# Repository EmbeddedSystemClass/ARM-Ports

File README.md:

Ports of some Communications Libraries to libopencm3
----------------------------------------------------

This project describes ports of CANfestival, FreeRTOS and freeMODBUS libraries
to work with libopencm3. ChaN's FAT filesystem has also been adapted to
libopencm3 but this is not maintained here. Refer to the [Battery Management
System repository](https://github.com/ksarkies/Battery-Management-System/tree/master/chan-fat-stm32-loc3).

In addition there are a number of sample programs designed to run with the
ET-STM32-STAMP and ET-STM32F103 development boards, and the STM32F4-Discovery
board.

* CanFestival-test
* FreeRTOS-usart-libopencm3
* test-can-ETSTM32STAMP
* test-cli
* test-libopencm3-stm32f1
* test-libopencm3-stm32f4
* test-sd-card-spi

More information is provided at:

(http://www.jiggerjuice.info/electronics/projects/arm/canfestival-stm32f103-port.html)

(http://www.jiggerjuice.info/electronics/projects/arm/freertos-stm32f103-port.html)

(http://www.jiggerjuice.info/electronics/projects/arm/modbus-stm32f103-port.html)

(http://www.jiggerjuice.info/electronics/projects/arm/chanfat-stm32f103-port.html)

(c) K. Sarkies 29/06/2015

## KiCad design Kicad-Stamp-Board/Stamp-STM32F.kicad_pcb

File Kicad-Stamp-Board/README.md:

STAMP Board for STM32F
----------------------

This project provides a STAMP board that is pin compatible with the ETT
ET-ARM-STAMP-STM32F103. This has advantages that it can be built into a
prototype system to provide the basic processor functions without having to
commit to any particular processor nor produce PCBs until the system under
development has been proven. The board improves on the ETT board by allowing
a range of processor families.

The board takes certain STM32F processors that use the LQFP64 footprint, as
these are largely pin compatible amongst a number of different families within
the STM32 range. Examples are:

STM32F10x. J5, J6, C15, C16 must all be shorted.
STM32L15x. J5, J6, C15, C16 must all be shorted.
STM32F2xx. J5, J6 must be shorted. C15 and C16 are 2.2uF capacitors.
STM32F4xx. J5, J6 must be shorted. C15 and C16 are 2.2uF capacitors.
STM32F72x. J5, J6, C15, C16 must all be shorted.
STM32F05x. Only C16 must be shorted, C15 and J5, J6, J14 left open.
STM32F30x. J5, C15, C16 must all be shorted, J6 left open.

STM32F37x and STM32F73x are not compatible as pin order is different.

In the second revision of the board, J5 on pin 48 and J6 on pin 18 are provided
so that STM32F05x and STM32F30x can be accommodated.

For any particular processor family, care must be taken to ensure full
compatibility with the board.

The Intersil ICL3221 was selected for RS232 driver as it is has low power
consumption and automatically powers down when no RS232 signals are detected.
It provides a single Rx/Tx pair. It also has the option to allow an external
signal to force power down but this is not used here. This single RS232
interface is provided mainly for programming.

For testing, when the PC serial cable is inserted, the Tx input from that sits
at about -6V. This triggers the device charge pumps to work. The voltages
expected are:

Pin 1 Enable Inv            Gnd
Pin 2 C1+ (C10)            5.96V
Pin 3 V+  (C12)            6.12V
Pin 4 C1- (C10)            3.1V
Pin 5 C2- (C14)            5.78V
Pin 6 C2+ (C14)            -0.3V
Pin 7 V-  (C13)            -5.6V
Pin 8 Tx in                -6V

(c) K. Sarkies 15/02/2018

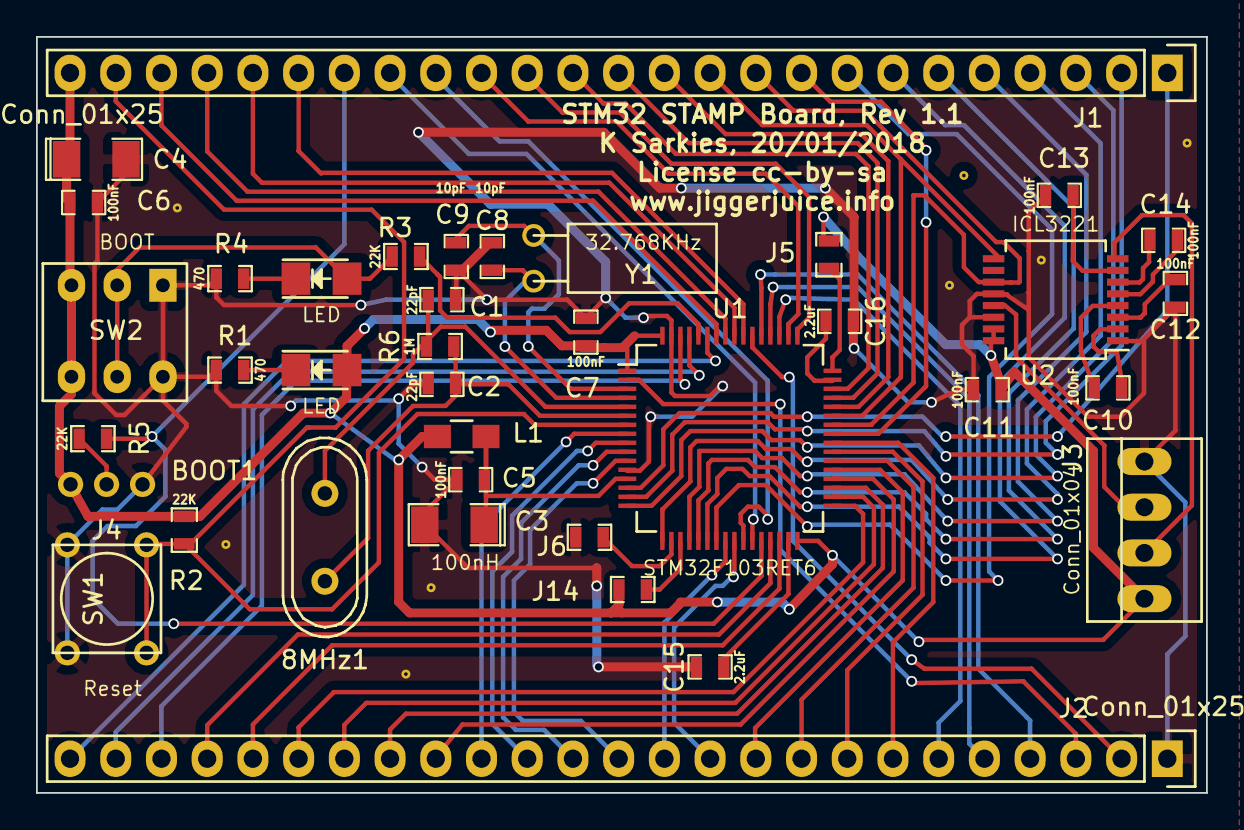
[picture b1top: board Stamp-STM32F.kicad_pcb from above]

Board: 2 copper layers, 65.0 x 42.0 mm, 46 parts (0 on the bottom side), 73 nets.

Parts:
8MHz1: 8MHz; Crystal_HC49-U_Vertical
C1, C2: 22pF; SM0603_Capa
C3, C4: 10uF; SM1206POL
C5, C6, C7, C10, C11, C12, C13, C14: 100nF; SM0603_Capa
C8, C9: 10pF; SM0603_Capa
C15, C16: 2.2uF; SM0603_Capa
D1, D2: LED; LED_1206
J1, J2: Conn_01x25; Pin_Header_Straight_1x25
J3: Conn_01x04; PINHEAD1-4
J4: BOOT1; pin_header_2mm_1x3
J5, J6, J14: Jumper; SM0603_Resistor
J7, J8, J9, J10, J11, J12, J13: Conn_01x01; THROUGHVIA
L1: 100nH; R_0805
R1, R4: 470; SM0603_Resistor
R2, R3, R5: 22K; SM0603_Resistor
R6: 1M; SM0603_Resistor
Ref**: Val**; THROUGHVIA
SW1: Reset; SW_PUSH_TINY
SW2: BOOT; SW_PB_DPDT
U1: STM32F103RET6; LQFP-64_10x10mm_Pitch0.5mm
U2: ICL3221; SSOP-16
Y1: 32.768KHz; Crystal_Watch

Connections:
3.3V: C4.1, C6.2, C7.1, C11.2, D1.2, J1.25, J3.1, J4.1, J5.2, J14.2, L1.1, R2.1, SW2.3, SW2.6, U1.1, U1.32, U1.64, U2.15, U2.16
Boot0: R3.2, U1.60
Earth: C1.2, C2.2, C3.2, C4.2, C5.1, C6.1, C7.2, C8.2, C9.2, C11.1, C12.2, C13.1, C15.2, C16.2, J2.1, J3.4, J4.3, J6.2, J7.1, J8.1, J9.1, J10.1, J11.1, J12.1, J13.1, R1.2, R4.1, SW1.1, SW2.1, SW2.4, U1.12, U1.63, U2.1, U2.12, U2.14
unnamed: 8MHz1.1, C1.1, R6.1, U1.5
unnamed: 8MHz1.2, C2.1, R6.2, U1.6
unnamed: C3.1, C5.2, L1.2, U1.13
unnamed: C8.1, U1.4, Y1.1
unnamed: C9.1, U1.3, Y1.2
unnamed: C10.1, U2.2
unnamed: C10.2, U2.4
unnamed: C12.1, U2.3
unnamed: C13.2, U2.7
unnamed: C14.1, U2.5
unnamed: C14.2, U2.6
unnamed: C15.1, U1.31
unnamed: C16.1, U1.47
unnamed: D1.1, R1.1
unnamed: D2.1, R4.2
unnamed: D2.2, R3.1, SW2.2, SW2.5
unnamed: J3.2, U2.8
unnamed: J3.3, U2.13
unnamed: J4.2, R5.1
unnamed: J5.1, U1.48
unnamed: J6.1, U1.18
unnamed: J14.1, U1.19
PA0: J1.1, U1.14
PA1: J1.2, U1.15
PA2: J1.3, U1.16
PA3: J1.4, U1.17
PA4: J1.5, U1.20
PA5: J1.6, U1.21
PA6: J1.7, U1.22
PA7: J1.8, U1.23
PA8: J1.9, U1.41
PA9: J1.10, U1.42, U2.11
PA10: J1.11, U1.43, U2.9
PA11: J1.12, U1.44
PA12: J1.13, U1.45
PA13: J1.14, U1.46
PA14: J1.15, U1.49
PA15: J1.16, U1.50
PB0: J1.17, U1.26
PB1: J1.18, U1.27
PB2: J1.19, R5.2, U1.28
PB3: J1.20, U1.55
PB4: J1.21, U1.56
PB5: J1.22, U1.57
PB6: J1.23, U1.58
PB7: J2.25, U1.59
PB8: J2.24, U1.61
PB9: J2.23, U1.62
PB10: J2.22, U1.29
PB11: J2.21, U1.30
PB12: J2.20, U1.33
PB13: J2.19, U1.34
PB14: J2.18, U1.35
PB15: J2.17, U1.36
PC0: J2.16, U1.8
PC1: J2.15, U1.9
PC2: J2.14, U1.10
PC3: J2.13, U1.11
PC4: J2.12, U1.24
PC5: J2.11, U1.25
PC6: J2.10, U1.37
PC7: J2.9, U1.38
PC8: J2.8, U1.39
PC9: J2.7, U1.40
PC10: J2.6, U1.51
PC11: J2.5, U1.52
PC12: J2.4, U1.53
PC13: J2.3, U1.2
PD2: J2.2, U1.54
RESET: J1.24, R2.2, SW1.2, U1.7

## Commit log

2015-06-29 Updates to newer versions of libopencm3
2015-06-29 Updates to remove drivers from CANfestival code into the port directory, update libopencm3 references and add README.
2016-01-22 Update all subprojects and examples to compile stage. Update README documentation
2016-01-22 Small correction to markdown
2016-01-24 Clean up all to compile stage with updated libopencm3 API
2016-02-09 Minor update to README
2016-03-02 Update READMEs for Markdown hyperlinks
2016-07-21 Add RTC test with CPU in deep sleep plus EXTI interrupts.
2016-07-21 Various doc mods and changes to makefiles for different load script
2017-12-08 Add Kicad STAMP board compatible with ET board but with more processor options.
2017-12-09 Small mods to PCB and README. Gerbers.
2017-12-25 Modify Kicad STAMP board to add two capacitors for compatibility with STM32F4xx and STM32F2xx. These are shorted to ground for STM32F1xx etc.
2017-12-26 Update README for Kicad STAMP
2018-01-18 Update PCB to allow more ground fill.
2018-01-19 Fix SSOP-16 footprint plus some adjustments to PCB
2018-01-20 Update PCB to stitch grounds a bit more. Update silk screen. Increase length of PCB to 70mm to satisfy fab house requirements.
2018-02-08 Update to some of the test code for changes in libopencm3 API.
2018-02-08 Minor change to STAMP schematic to label resistor correctly.
2018-02-12 Introduce test-ports to exercise each port as output for hardware testing. Add stm32-h103R4.ld for very low density device. Fix test-cli to setup hardware only as required for the test.
2018-02-15 Update test-ports to add a pin short test and deal with PA10.
2018-02-15 Update to README for STAMP board.
2018-02-16 Update PCB to add a jumper on each of pins 48 and 18 to accommodate additional STM32 families.
2018-03-28 Add another jumper to cater for STM32F051.
2018-04-15 Add more test-ports code to deal with STM32L1xx and STM32F4xx

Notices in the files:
Kicad-Stamp-Board/Stamp-STM32F.kicad_pcb:
License cc-by-sa
